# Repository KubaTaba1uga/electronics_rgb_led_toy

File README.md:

# RGB LED Toy

A simple project demonstrating how an RGB LED works. By adjusting potentiometers, users can mix red, green, and blue light to create any color in the RGB spectrum.

## Table of Contents

- [Overview](#overview)
- [Features](#features)
- [Hardware Components](#hardware-components)
- [Enclosure Design](#enclosure-design)
- [Getting Started](#getting-started)
- [Assembly Instructions](#assembly-instructions)
- [Usage](#usage)
- [Contributing](#contributing)
- [License](#license)
- [Acknowledgments](#acknowledgments)

## Overview

This project consists of a PCB board designed in KiCad and an enclosure designed in OpenSCAD, which can be 3D printed. The circuit allows users to adjust the intensity of red, green, and blue channels of an RGB LED using potentiometers, creating a full range of colors.

## Features

- **RGB Color Mixing**: Adjust potentiometers to mix red, green, and blue light.
- **Custom PCB Design**: PCB board designed using KiCad.
- **3D Printable Enclosure**: Box designed in OpenSCAD for housing the PCB and components.

## Hardware Components

- **Electronics**:
  - 1 x Common Cathode RGB LED
  - 3 x Potentiometers (e.g., 10kΩ linear taper)
  - 3 x Current-limiting resistors for the RGB LED (calculate based on your LED specs)
  - 3 x Rocker switches
  - 1 x PCB (design files included)
  - 3 x AAA battery
  - Wires and connectors as needed
  - Some M2 screws
- **Tools Required**:
  - Soldering iron and solder
  - Wire cutters/strippers
  - Multimeter (optional for testing)

Components examples:
- [Red rocker switch](https://www.amazon.com/Twidec-Rocker-Position-Illuminated-KCD2-201N-BU/dp/B07MV5LBX8/ref=sr_1_1?crid=3TD23RVLMG6Z4&dib=eyJ2IjoiMSJ9.MytuyUmSVyDPcqdz0-hPTGBWjusLBUMxMacKpkE82gv4jepQVEn_gehBBpbBIvG3z0AbFAFO2Uk4pilC01WHr0K3-53ic8luo5b2fuP7ekoIxj79-xcMwD2pG09d9zLjWrHabZ0-CDp8GRCul-4eHnmPWNCAGQE1n28UB6E4wumrJ58iK5A6zx9YEQmL51N7-F1vKiq0_7a-CcSb2CmqyDhs0_pPEpygn4H0GRY7VEU.NOZqBpuaGICAkMl2GmvqS3otJYxrt7sDQj98gaYhyTk&dib_tag=se&keywords=Rocker%2BSwitch%2BDPST%2Bblue&qid=1732781497&sprefix=rocker%2Bswitch%2Bdpst%2Bblu%2Caps%2C201&sr=8-1&th=1)
- [Blue rocker switch](https://www.amazon.com/Twidec-Rocker-Position-Illuminated-KCD2-201N-BU/dp/B08YNQX96T/ref=sr_1_1?crid=3TD23RVLMG6Z4&dib=eyJ2IjoiMSJ9.MytuyUmSVyDPcqdz0-hPTGBWjusLBUMxMacKpkE82gv4jepQVEn_gehBBpbBIvG3z0AbFAFO2Uk4pilC01WHr0K3-53ic8luo5b2fuP7ekoIxj79-xcMwD2pG09d9zLjWrHabZ0-CDp8GRCul-4eHnmPWNCAGQE1n28UB6E4wumrJ58iK5A6zx9YEQmL51N7-F1vKiq0_7a-CcSb2CmqyDhs0_pPEpygn4H0GRY7VEU.NOZqBpuaGICAkMl2GmvqS3otJYxrt7sDQj98gaYhyTk&dib_tag=se&keywords=Rocker%2BSwitch%2BDPST%2Bblue&qid=1732781497&sprefix=rocker%2Bswitch%2Bdpst%2Bblu%2Caps%2C201&sr=8-1&th=1)
- [Green rocker switch](https://www.amazon.com/Twidec-Rocker-Position-Illuminated-KCD2-201N-BU/dp/B07MV5TVKX/ref=sr_1_1?crid=3TD23RVLMG6Z4&dib=eyJ2IjoiMSJ9.MytuyUmSVyDPcqdz0-hPTGBWjusLBUMxMacKpkE82gv4jepQVEn_gehBBpbBIvG3z0AbFAFO2Uk4pilC01WHr0K3-53ic8luo5b2fuP7ekoIxj79-xcMwD2pG09d9zLjWrHabZ0-CDp8GRCul-4eHnmPWNCAGQE1n28UB6E4wumrJ58iK5A6zx9YEQmL51N7-F1vKiq0_7a-CcSb2CmqyDhs0_pPEpygn4H0GRY7VEU.NOZqBpuaGICAkMl2GmvqS3otJYxrt7sDQj98gaYhyTk&dib_tag=se&keywords=Rocker%2BSwitch%2BDPST%2Bblue&qid=1732781497&sprefix=rocker%2Bswitch%2Bdpst%2Bblu%2Caps%2C201&sr=8-1&th=1)

## Enclosure Design

The enclosure is designed in OpenSCAD and can be 3D printed. The design files are available in the `openscad_src` directory. Ensure your 3D printer is calibrated correctly for precise fitting of components.

## Getting Started

1. **Clone the Repository**: Clone this repository to your local machine using `git clone https://github.com/KubaTaba1uga/electronics_rgb_led_toy.git`.
2. **Review the Schematics**: Open the KiCad files located in the `kicad_src` directory to understand the circuit design.
3. **Prepare the PCB**: Manufacture the PCB using the provided design files or use a prototyping board for initial testing.
4. **Gather Components**: Ensure all necessary components are available before assembly.

## Assembly Instructions

1. **Solder Components**: Solder the RGB LED, potentiometers, resistors, and connectors onto the PCB as per the schematic.
2. **Assemble Enclosure**: 3D print the enclosure and place the assembled PCB inside, securing it appropriately.

## Usage

- **Adjust Colors**: Rotate the potentiometers to vary the intensity of each color channel (red, green, blue) and observe the resulting color from the RGB LED.
- **Experiment**: Mix different levels to create various colors and understand additive color mixing principles.

## Contributing

Contributions are welcome! Please fork the repository and create a pull request with your proposed changes. Ensure your code adheres to the project's coding standards and includes appropriate documentation.

## License

This project is licensed under the MIT License. See the [LICENSE](LICENSE) file for more details.

## Acknowledgments

- Inspired by basic electronics and the desire to make learning interactive.
- Thanks to the communities of [KiCad](https://www.kicad.org/) and [OpenSCAD](https://www.openscad.org/) for their amazing tools.
- Thanks to Charles platt (Make: Electronics) and Paul Sherz, Simon Monk (Practical Electronics for Inventors) for their awesome books.

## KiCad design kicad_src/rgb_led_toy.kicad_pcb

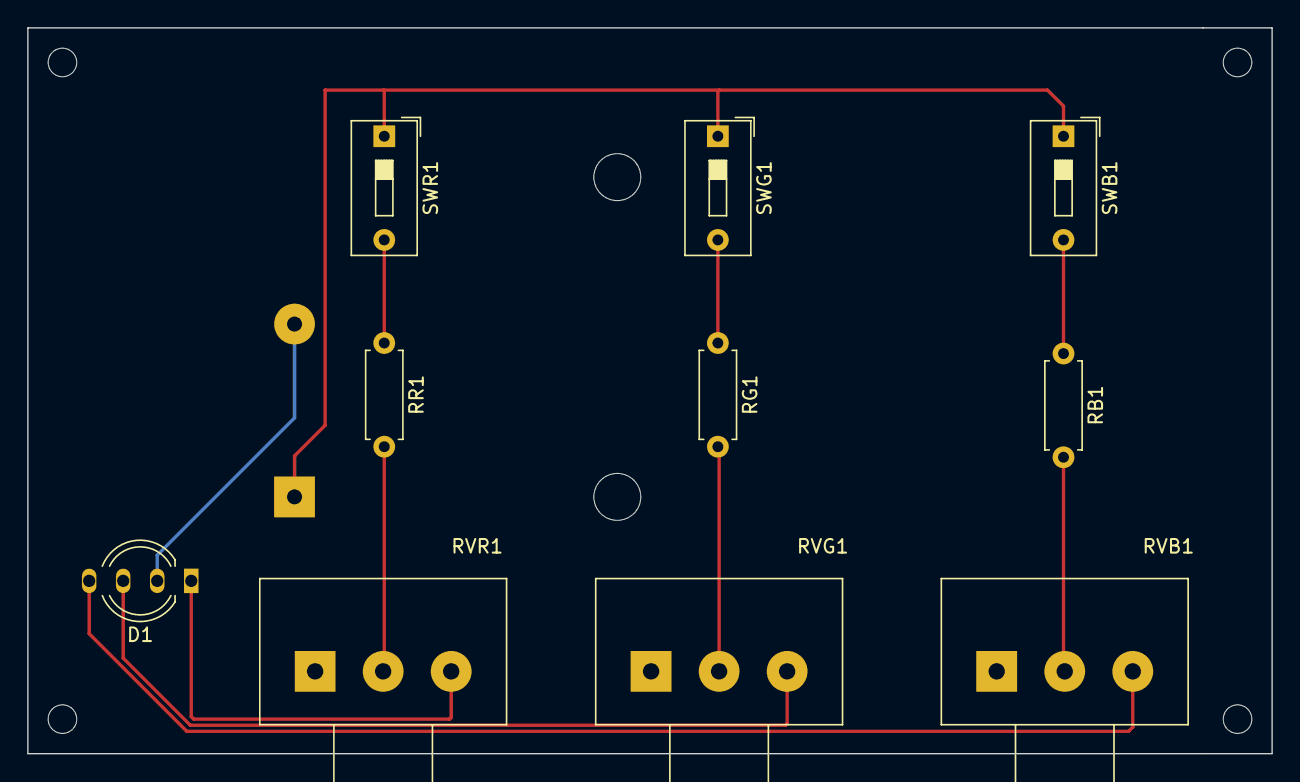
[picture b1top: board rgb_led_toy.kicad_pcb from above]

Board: 2 copper layers, 91.4 x 53.3 mm, 11 parts (1 on the bottom side), 11 nets.

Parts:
BT1: 4.5V; BatteryHolder_Keystone_2479_3xAAA
D1: LED_RGBK; LED_D10.0mm-4_RGB
RB1: 68 Ohm; R_Axial_DIN0207_L6.3mm_D2.5mm_P7.62mm_Horizontal
RG1: 100 Ohm; R_Axial_DIN0207_L6.3mm_D2.5mm_P7.62mm_Horizontal
RR1: 120 Ohm; R_Axial_DIN0207_L6.3mm_D2.5mm_P7.62mm_Horizontal
RVB1: 10k Ohm; Potentiometer_Alps_RK163_Single_Horizontal
RVG1: 10k Ohm; Potentiometer_Alps_RK163_Single_Horizontal
RVR1: 10k Ohm; Potentiometer_Alps_RK163_Single_Horizontal
SWB1: SW_SPST; SW_DIP_SPSTx01_Slide_9.78x4.72mm_W7.62mm_P2.54mm
SWG1: SW_SPST; SW_DIP_SPSTx01_Slide_9.78x4.72mm_W7.62mm_P2.54mm
SWR1: SW_SPST; SW_DIP_SPSTx01_Slide_9.78x4.72mm_W7.62mm_P2.54mm

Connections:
GND: BT1.2 (-), D1.2 (BA)
unnamed: BT1.1 (+), SWB1.1 (A), SWG1.1 (A), SWR1.1 (A)
unnamed: D1.1 (K), RVR1.3
unnamed: D1.3 (GA), RVG1.3
unnamed: D1.4 (RA), RVB1.3
unnamed: RB1.1, SWB1.2 (B)
unnamed: RB1.2, RVB1.2
unnamed: RG1.1, SWG1.2 (B)
unnamed: RG1.2, RVG1.2
unnamed: RR1.1, SWR1.2 (B)
unnamed: RR1.2, RVR1.2

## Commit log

2024-11-28 init project
2024-11-28 add scad project, external libs missing
2024-11-28 add task to download external libs for openscad
2024-11-29 add task to open openscad project
2024-11-29 add kicad project and command to build it
2024-11-29 add openscad project generation
2024-11-29 improve build
2024-11-29 cleanup
2024-11-29 add project license
2024-11-29 add image
